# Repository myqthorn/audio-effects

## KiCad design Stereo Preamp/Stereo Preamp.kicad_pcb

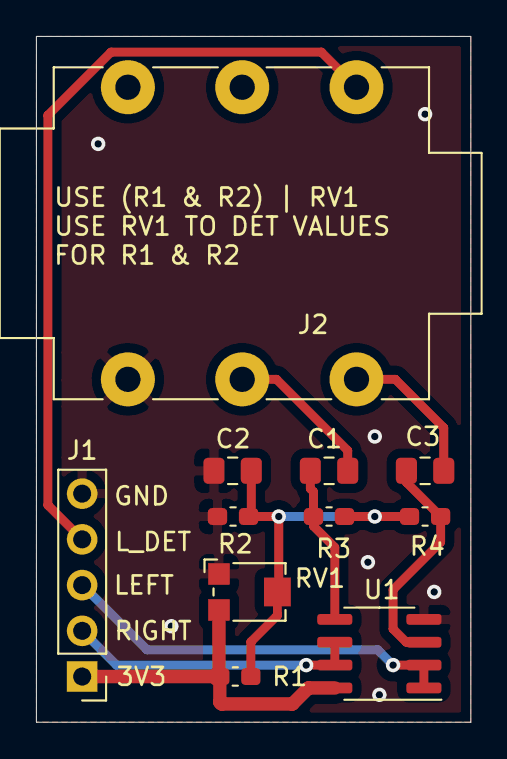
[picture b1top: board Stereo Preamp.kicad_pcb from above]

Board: 2 copper layers, 24.1 x 38.1 mm, 11 parts (0 on the bottom side), 10 nets.

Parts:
C1, C3: 100n; C_0805_2012Metric_Pad1.18x1.45mm_HandSolder
C2: 10u; C_0805_2012Metric_Pad1.18x1.45mm_HandSolder
J1: Conn_01x05; PinHeader_1x05_P2.54mm_Vertical
J2: AudioJack3_Ground_Switch; Jack_6.35mm_Neutrik_NMJ6HCD2_Horizontal
R1, R2: 100k; C_0603_1608Metric_Pad1.08x0.95mm_HandSolder
R3, R4: 560k; C_0603_1608Metric_Pad1.08x0.95mm_HandSolder
RV1: 200k; Potentiometer_Bourns_TC33X_Vertical
U1: MCP6002-xSN; SOIC-8_3.9x4.9mm_P1.27mm

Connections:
+3V3: J1.1, R1.1, RV1.3, U1.8
/L_DETECT: J1.4, J2.TN
/L_OUT: J1.3, U1.1, U1.2
/R_OUT: J1.2, U1.6, U1.7
GND: C2.2, J1.5, J2.S, R2.2, RV1.1, U1.4
unnamed: C1.1, J2.R
unnamed: C1.2, R3.1, U1.5
unnamed: C2.1, R1.2, R2.1, R3.2, R4.1, RV1.2
unnamed: C3.1, J2.T
unnamed: C3.2, R4.2, U1.3

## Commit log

2021-02-17 Stereo Preamp KiCad files
2021-02-17 removed space from names
